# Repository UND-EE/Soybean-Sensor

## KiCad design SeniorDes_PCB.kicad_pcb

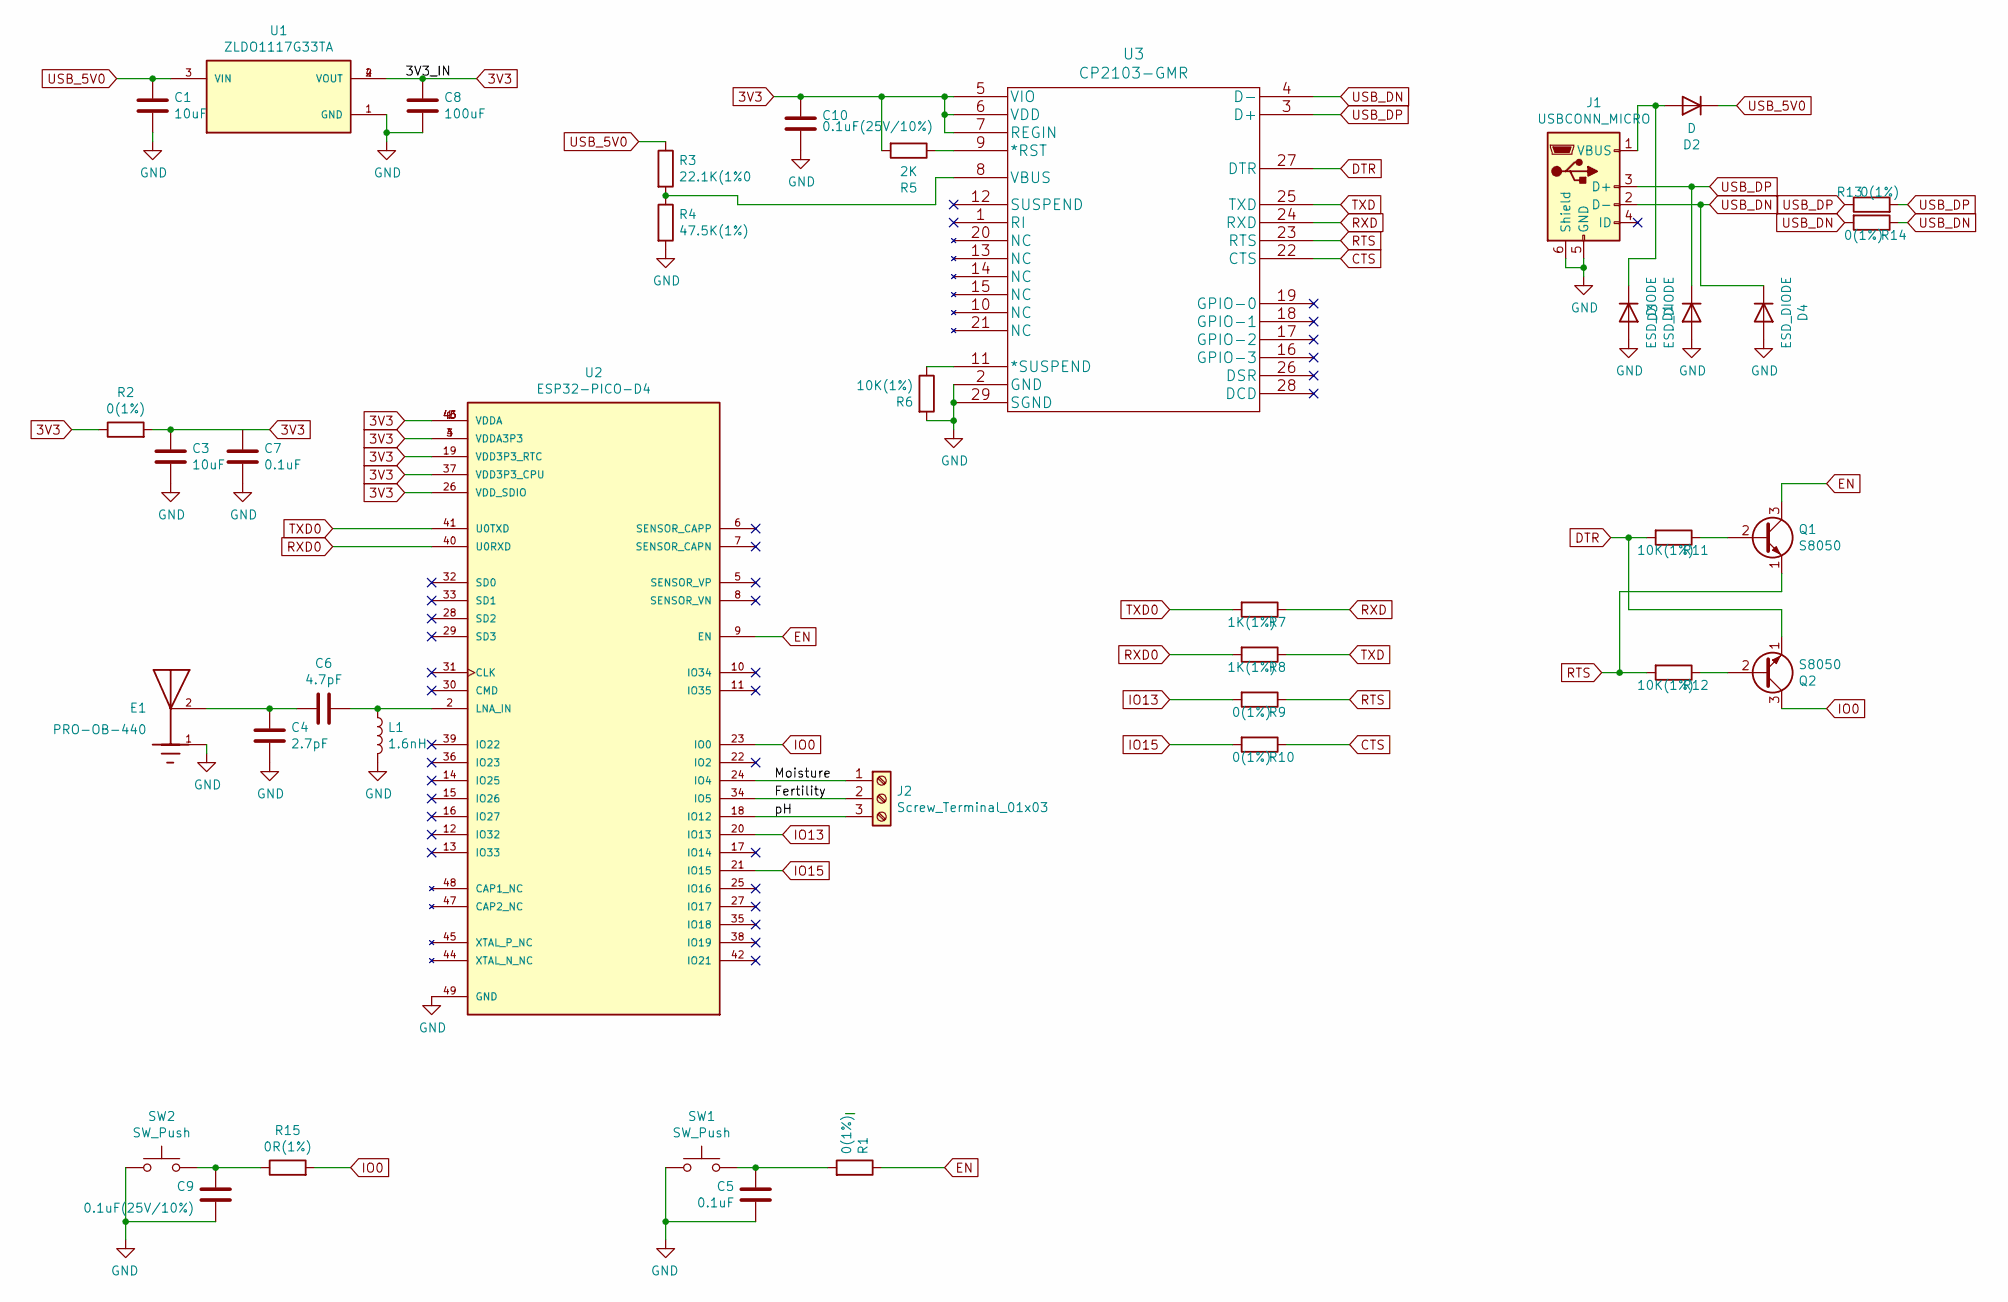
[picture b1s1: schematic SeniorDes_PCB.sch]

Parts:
C1, C3: 10uF; C_0603_1608Metric
C4: 2.7pF; C_0402_1005Metric
C5, C7: 0.1uF; C_0402_1005Metric
C6: 4.7pF; C_0402_1005Metric
C8: 100uF; C_0603_1608Metric
C9, C10: 0.1uF(25V/10%); C_0402_1005Metric
D1, D3, D4: ESD_DIODE; D_0805_2012Metric
D2: D; D_0805_2012Metric
E1: PRO-OB-440; PARTREV 3.2
J1: USBCONN_MICRO; USB_Micro-B_Molex-105017-0001
J2: Screw_Terminal_01x03; TerminalBlock_Altech_AK300-3_P5.00mm
L1: 1.6nH; L_0603_1608Metric
Q1, Q2: S8050; TO-92_Inline
R1, R2, R9, R10, R13, R14: 0(1%); R_0402_1005Metric
R3: 22.1K(1%0; R_0402_1005Metric
R4: 47.5K(1%); R_0402_1005Metric
R5: 2K; R_0402_1005Metric
R6, R11, R12: 10K(1%); R_0402_1005Metric
R7, R8: 1K(1%); R_0402_1005Metric
R15: 0R(1%); R_0402_1005Metric
SW1, SW2: SW_Push; Panasonic_EVQPUJ_EVQPUA
U1: ZLDO1117G33TA; SOT230P700X180-4N; PARTREV 6-2
U2: ESP32-PICO-D4; PQFN50P700X700X104-49N; PARTREV v1.9
U3: CP2103-GMR

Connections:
3V3: C3.1, C7.1, C8.1, C10.1, R2.1, R2.2, R5.2, U1.2 (VOUT), U1.4 (VOUT), U2.1 (VDDA), U2.3 (VDDA3P3), U2.4 (VDDA3P3), U2.19 (VDD3P3_RTC), U2.26 (VDD_SDIO), U2.37 (VDD3P3_CPU), U2.43 (VDDA), U2.46 (VDDA), U3.5 (VIO), U3.6 (VDD), U3.7 (REGIN)
/Fertility: J2.2, U2.34 (IO5)
/Moisture: J2.1, U2.24 (IO4)
/pH: J2.3, U2.18 (IO12)
CTS: R10.1, U3.22 (CTS)
DTR: Q2.1 (E), R11.2, U3.27 (DTR)
EN: Q1.3 (C), R1.1, U2.9 (EN)
GND: C1.2, C3.2, C4.2, C5.2, C7.2, C8.2, C9.2, C10.2, D1.2 (A), D3.2 (A), D4.2 (A), E1.1, J1.5 (GND), J1.6 (Shield), L1.2, R4.2, R6.2, SW1.2, SW2.2, U1.1 (GND), U2.49 (GND), U3.2 (GND), U3.29 (SGND)
IO0: Q2.3 (C), R15.2, U2.23 (IO0)
IO13: R9.2, U2.20 (IO13)
IO15: R10.2, U2.21 (IO15)
unnamed: C4.1, C6.1, E1.2
unnamed: C5.1, R1.2, SW1.1
unnamed: C6.2, L1.1, U2.2 (LNA_IN)
unnamed: C9.1, R15.1, SW2.1
unnamed: D1.1 (K), D2.2 (A), J1.1 (VBUS)
unnamed: Q1.2 (B), R11.1
unnamed: Q2.2 (B), R12.1
unnamed: R3.2, R4.1, U3.8 (VBUS)
unnamed: R5.1, U3.9 (*RST)
unnamed: R6.1, U3.11 (*SUSPEND)
RTS: Q1.1 (E), R9.1, R12.2, U3.23 (RTS)
RXD: R7.1, U3.24 (RXD)
RXD0: R8.2, U2.40 (U0RXD)
TXD: R8.1, U3.25 (TXD)
TXD0: R7.2, U2.41 (U0TXD)
USB_5V0: C1.1, D2.1 (K), R3.1, U1.3 (VIN)
USB_DN: D4.1 (K), J1.2 (D-), R14.1, R14.2, U3.4 (D-)
USB_DP: D3.1 (K), J1.3 (D+), R13.1, R13.2, U3.3 (D+)

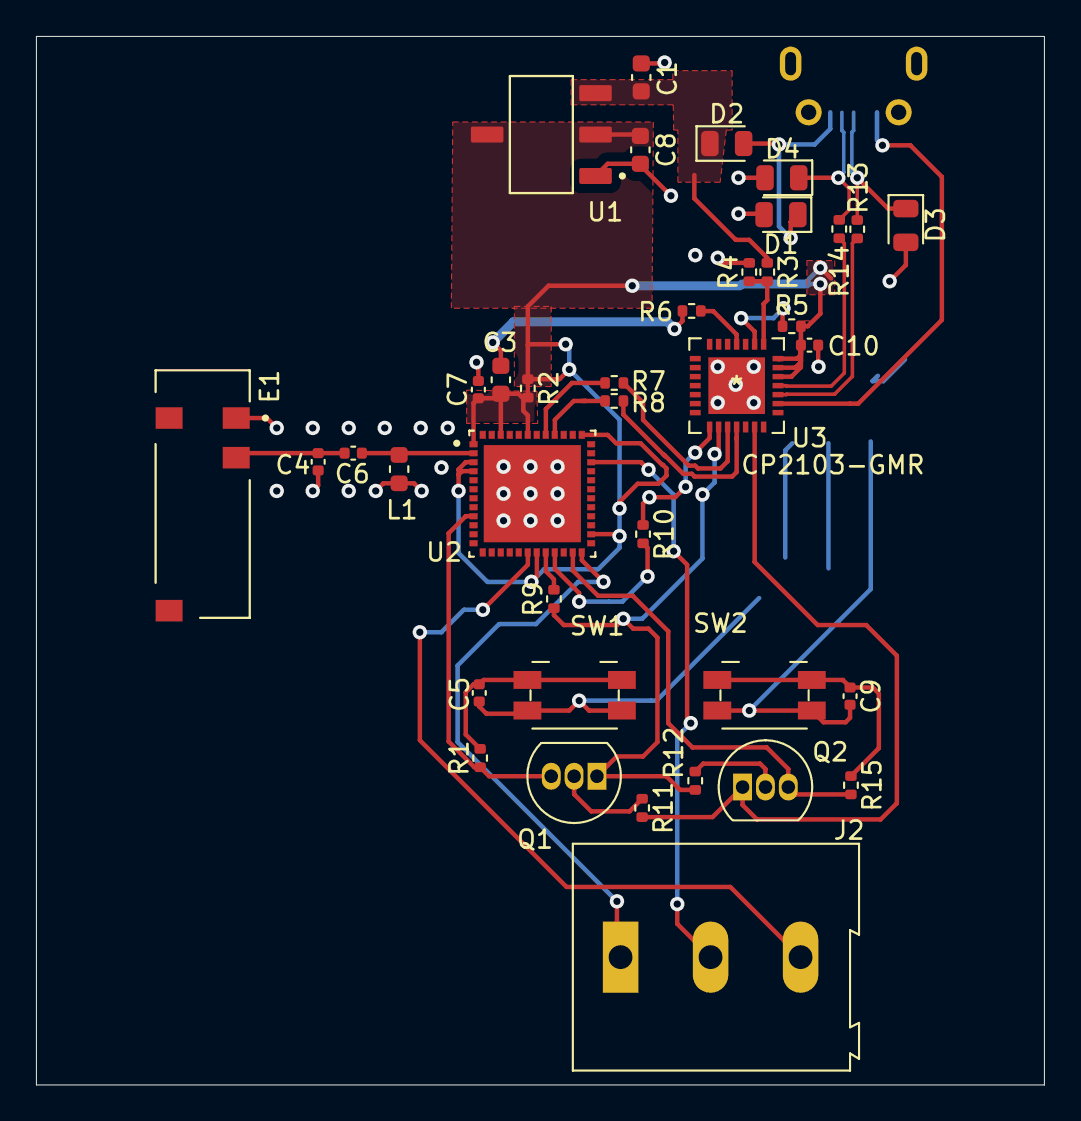
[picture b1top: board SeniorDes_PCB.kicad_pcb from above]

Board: 2 copper layers, 56.0 x 58.2 mm, 39 parts (1 on the bottom side), 29 nets.

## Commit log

2021-12-16 Add files via upload
    Intial Release -

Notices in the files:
parts and their libraries:
Copyright 2021 Accelerated Designs. All rights reserved.
